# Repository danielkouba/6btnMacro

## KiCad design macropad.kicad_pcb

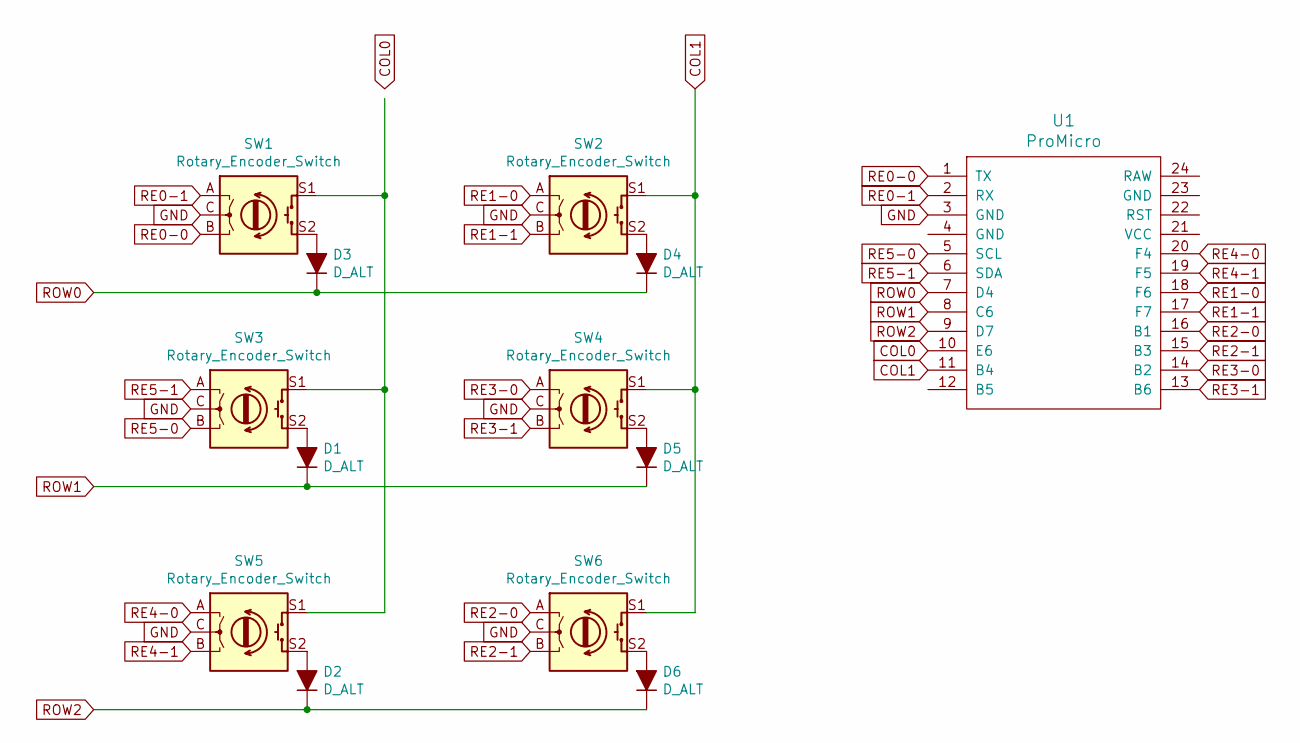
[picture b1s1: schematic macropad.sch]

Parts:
D1, D2, D3, D4, D5, D6: D_ALT; Diode
SW1, SW2, SW3, SW4, SW5, SW6: Rotary_Encoder_Switch; RotaryEncoder_MX
U1: ProMicro

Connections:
COL0: U1.10 (E6)
COL1: SW2.S1, SW4.S1, SW6.S1, U1.11 (B4)
GND: SW1.C, SW2.C, SW3.C, SW4.C, SW5.C, SW6.C, U1.3 (GND)
unnamed: D1.2 (A), SW3.S2
unnamed: D2.2 (A), SW5.S2
unnamed: D3.2 (A), SW1.S2
unnamed: D4.2 (A), SW2.S2
unnamed: D5.2 (A), SW4.S2
unnamed: D6.2 (A), SW6.S2
unnamed: SW1.S1, SW3.S1, SW5.S1
RE0-0: SW1.B, U1.1 (TX)
RE0-1: SW1.A, U1.2 (RX)
RE1-0: SW2.A, U1.18 (F6)
RE1-1: SW2.B, U1.17 (F7)
RE2-0: SW6.A, U1.16 (B1)
RE2-1: SW6.B, U1.15 (B3)
RE3-0: SW4.A, U1.14 (B2)
RE3-1: SW4.B, U1.13 (B6)
RE4-0: SW5.A, U1.20 (F4)
RE4-1: SW5.B, U1.19 (F5)
RE5-0: SW3.B, U1.5 (SCL)
RE5-1: SW3.A, U1.6 (SDA)
ROW0: D3.1 (K), D4.1 (K), U1.7 (D4)
ROW1: D1.1 (K), D5.1 (K), U1.8 (C6)
ROW2: D2.1 (K), D6.1 (K), U1.9 (D7)

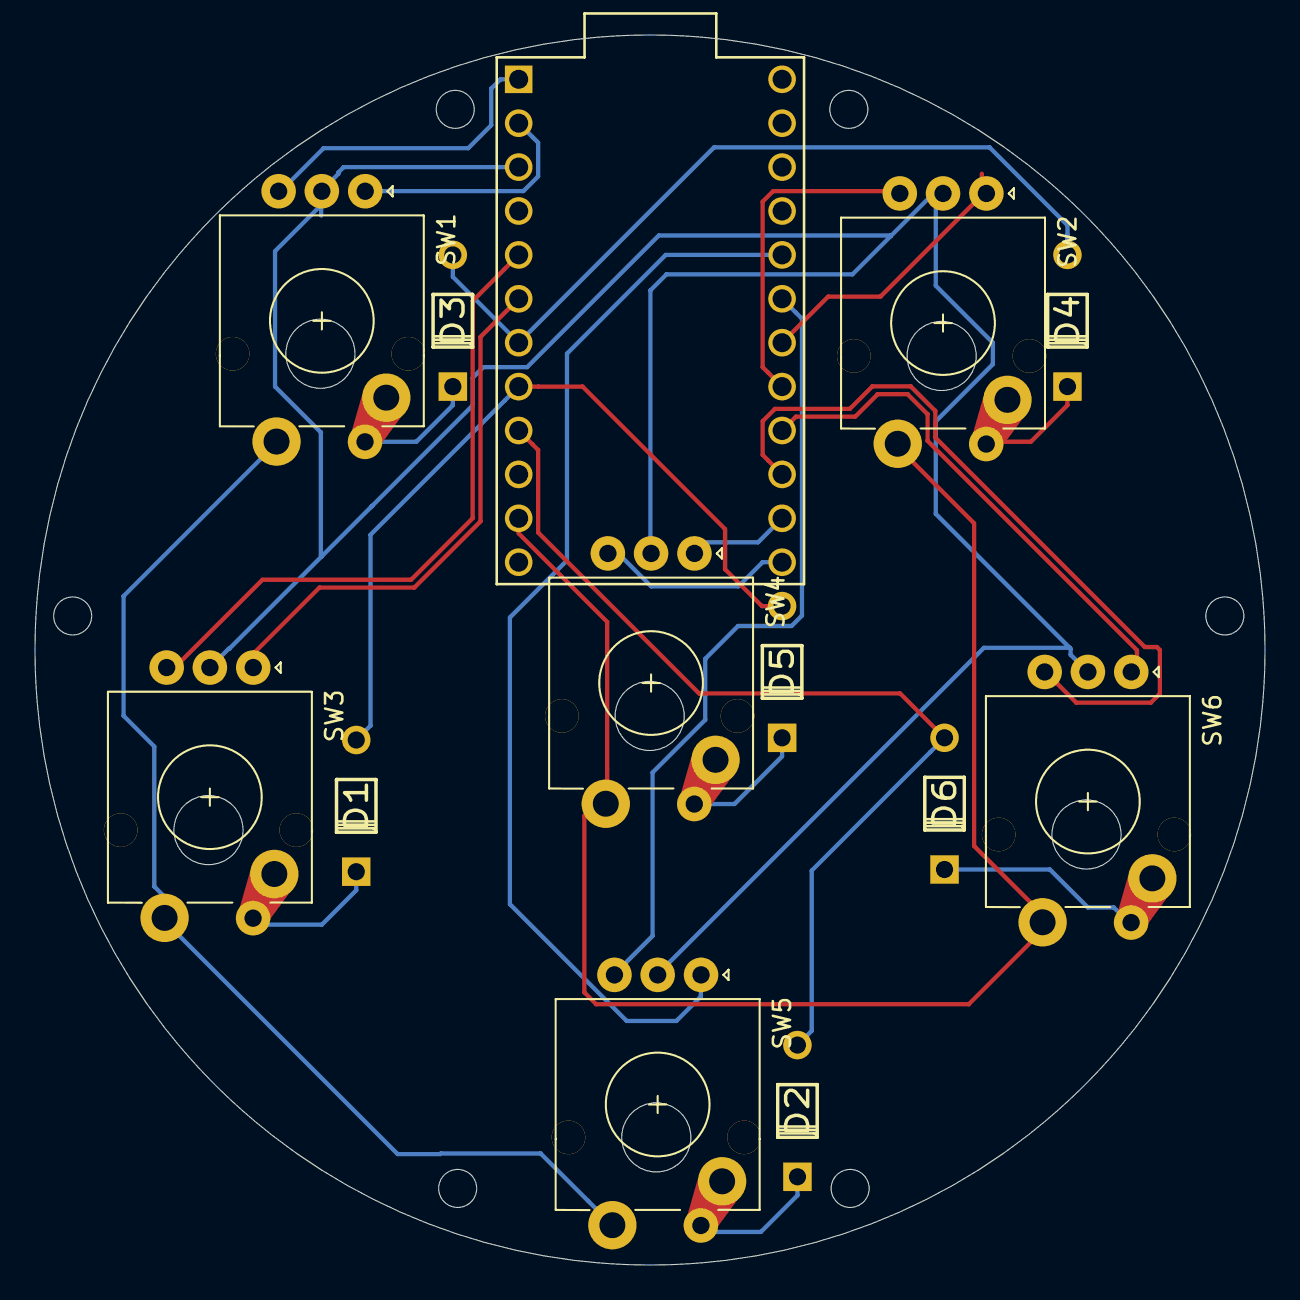
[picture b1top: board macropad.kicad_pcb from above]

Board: 2 copper layers, 71.2 x 71.2 mm, 19 parts (0 on the bottom side), 24 nets.

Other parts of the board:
HOLE_M2, HOLE_M2#2, HOLE_M2#3, HOLE_M2#4, HOLE_M2#5, HOLE_M2#6: VAL**; HOLE_M2

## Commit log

2019-09-12 adding project files
2019-09-12 Added diodes
2019-09-12 added keebio part libraries
2019-09-12 added some wires
2019-09-13 finished wiring and assigned footprints
2019-09-13 Started designing pcb
2019-09-13 moved to 70mm circle, just before routing
2019-09-16 finished first pass routing
2019-09-17 Created new footprint and fixed routing
2019-09-20 first print
2019-09-23 fixing printing mistakes
